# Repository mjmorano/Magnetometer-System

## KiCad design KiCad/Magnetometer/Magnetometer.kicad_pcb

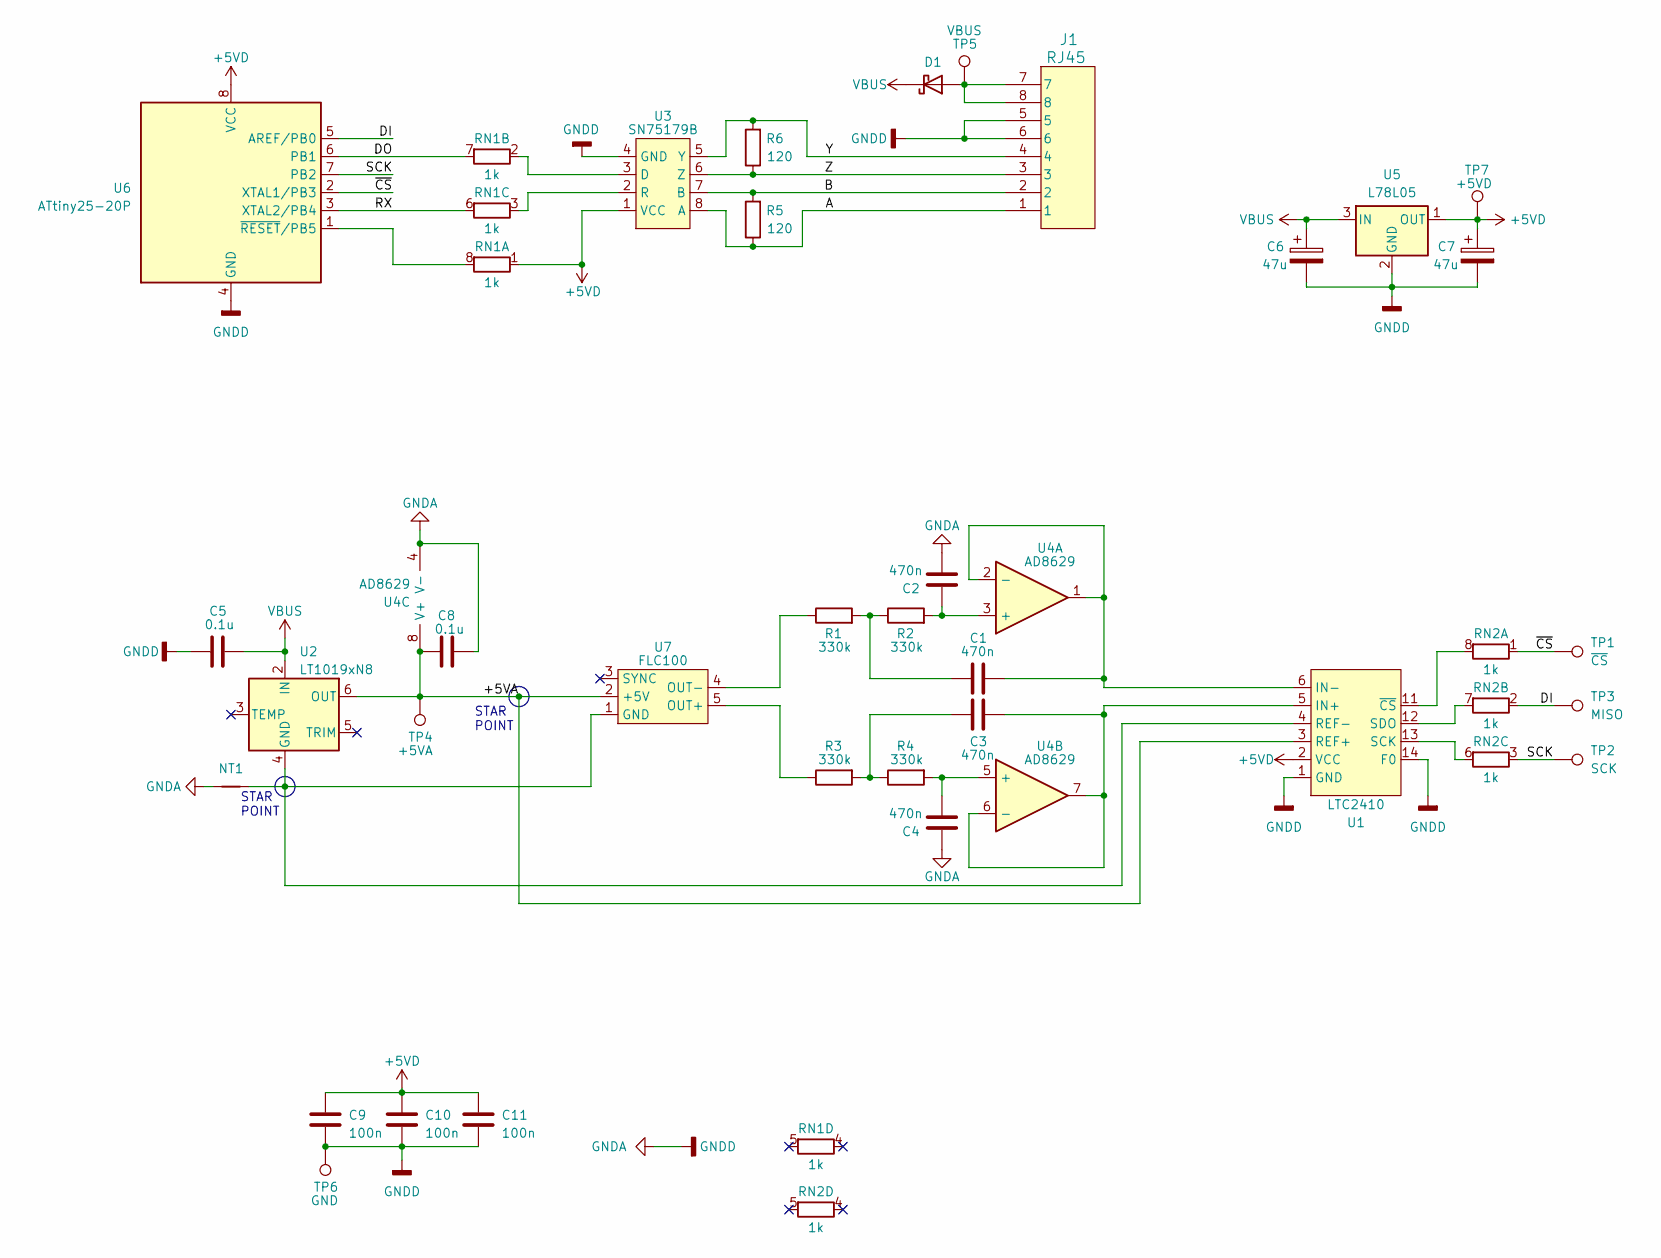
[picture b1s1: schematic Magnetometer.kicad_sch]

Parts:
C1, C2, C3, C4: 470n; C_1206_3216Metric
C5, C8: 0.1u; C_0603_1608Metric
C6, C7: 47u; CP_EIA-6032-28_Kemet-C
C9, C10, C11: 100n; C_0603_1608Metric
D1: D_Schottky; D_SOD-123F
J1: RJ45; rj45
NT1: NetTie-2_SMD_Pad0.5mm
R1, R2, R3, R4: 330k; R_0603_1608Metric
R5, R6: 120; R_0603_1608Metric
RN1, RN2: 1k; R_Array_Convex_4x0603
TP1: ~{CS}; TestPoint_Pad_D1.0mm
TP2: SCK; TestPoint_Pad_D1.0mm
TP3: MISO; TestPoint_Pad_D1.0mm
TP4: +5VA; TestPoint_Pad_D1.0mm
TP5: VBUS; TestPoint_Pad_D1.0mm
TP6: GND; TestPoint_Pad_D1.0mm
TP7: +5VD; TestPoint_Pad_D1.0mm
U1: LTC2410; SSOP-16_3.9x4.9mm_P0.635mm
U2: LT1019xN8; SOIC-8_3.9x4.9mm_P1.27mm
U3: SN75179B; SOIC-8_3.9x4.9mm_P1.27mm
U4: AD8629; SOIC-8_3.9x4.9mm_P1.27mm
U5: L78L05; SOT-89-3
U6: ATtiny25-20P; DIP-8_W7.62mm
U7: FLC100

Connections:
+5VD: C7.1, C9.1, C10.1, C11.1, RN1.1 (R1.1), TP7.1, U1.2 (VCC), U3.1 (VCC), U5.1 (OUT), U6.8 (VCC)
/+5VA: C8.1, TP4.1, U1.3 (REF+), U2.6 (OUT), U4.8 (V+), U7.2 (+5V)
/A: J1.1, R5.1, U3.8 (A)
/B: J1.2, R5.2, U3.7 (B)
/DI: RN2.2 (R2.1), TP3.1, U6.5 (AREF/PB0)
/DO: RN1.7 (R2.2), U6.6 (PB1)
/RX: RN1.6 (R3.2), U6.3 (XTAL2/PB4)
/SCK: RN2.3 (R3.1), TP2.1, U6.7 (PB2)
/Y: J1.4, R6.2, U3.5 (Y)
/Z: J1.3, R6.1, U3.6 (Z)
/~CS: RN2.1 (R1.1), TP1.1, U6.2 (XTAL1/PB3)
GNDA: C2.2, C4.1, C5.2, C6.2, C7.2, C8.2, C9.2, C10.2, C11.2, J1.5, J1.6, NT1.2, TP6.1, U1.1 (GND), U1.7 (GND), U1.8 (GND), U1.9 (GND), U1.10 (GND), U1.14 (F0), U1.15 (GND), U1.16 (GND), U3.4 (GND), U4.4 (V-), U5.2 (GND), U6.4 (GND)
unnamed: C1.2, R1.2, R2.1
unnamed: C3.2, R3.2, R4.1
unnamed: D1.2 (A), J1.7, J1.8, TP5.1
unnamed: RN1.8 (R1.2), U6.1 (~RESET/PB5)
unnamed: RN1.2 (R2.1), U3.3 (D)
unnamed: RN1.3 (R3.1), U3.2 (R)
unnamed: RN2.8 (R1.2), U1.11 (~CS)
unnamed: RN2.7 (R2.2), U1.12 (SDO)
unnamed: RN2.6 (R3.2), U1.13 (SCK)
unnamed: C3.1, U1.5 (IN+), U4.6 (-), U4.7
unnamed: C1.1, U1.6 (IN-), U4.1, U4.2 (-)
unnamed: NT1.1, U1.4 (REF-), U2.4 (GND), U7.1 (GND)
unnamed: C2.1, R2.2, U4.3 (+)
unnamed: C4.2, R4.2, U4.5 (+)
unnamed: R3.1, U7.5 (OUT+)
unnamed: R1.1, U7.4 (OUT-)
VBUS: C5.1, C6.1, D1.1 (K), U2.2 (IN), U5.3 (IN)

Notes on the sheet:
STAR POINT

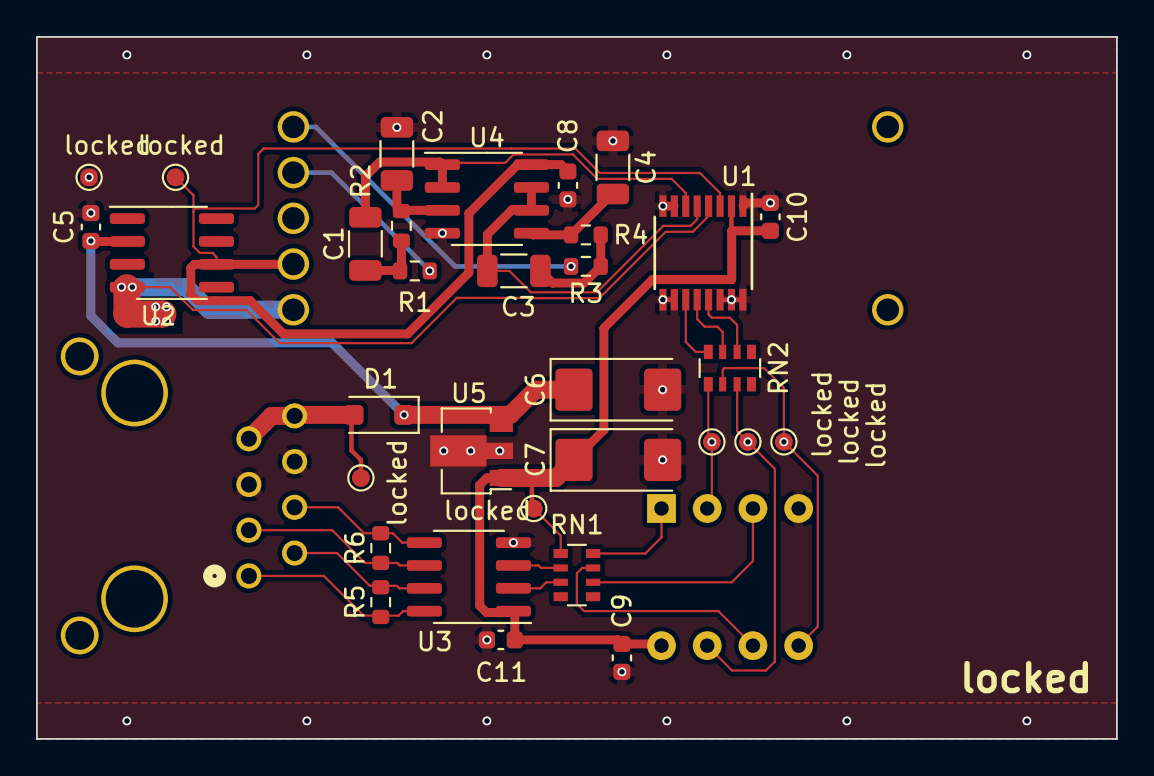
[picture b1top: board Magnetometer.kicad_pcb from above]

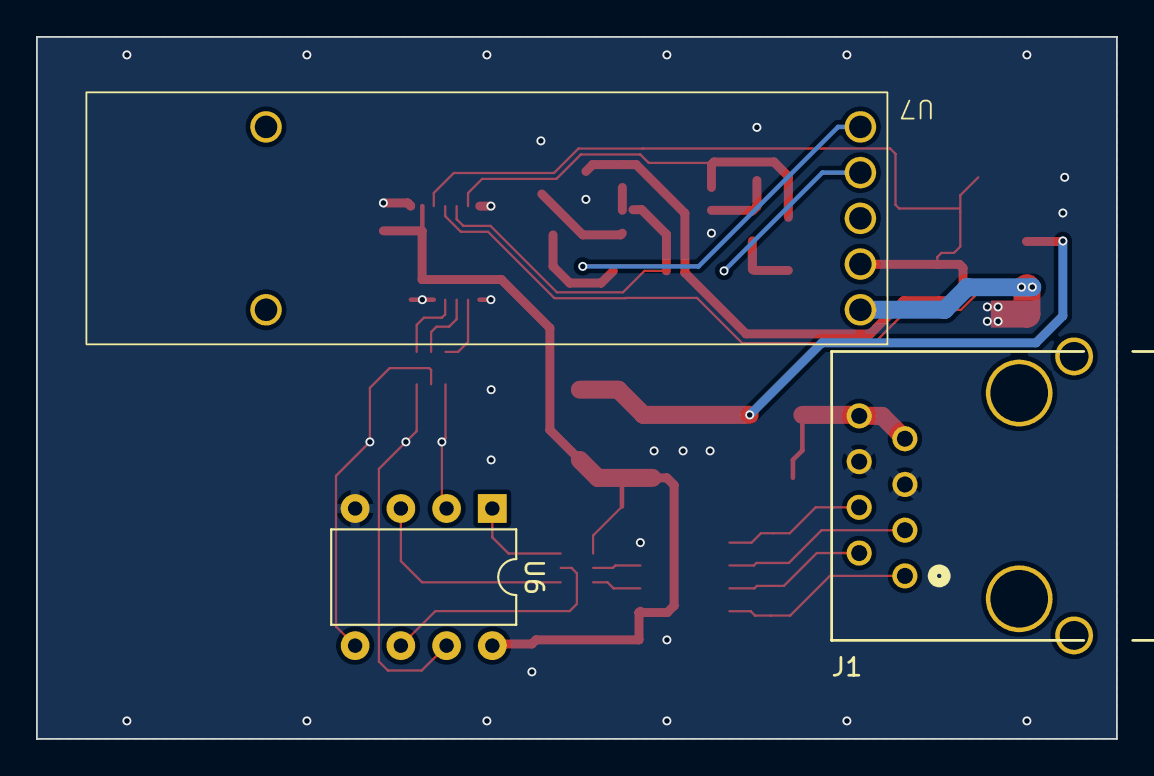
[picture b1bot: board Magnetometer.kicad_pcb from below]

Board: 2 copper layers, 60.0 x 39.0 mm, 36 parts (3 on the bottom side), 29 nets.

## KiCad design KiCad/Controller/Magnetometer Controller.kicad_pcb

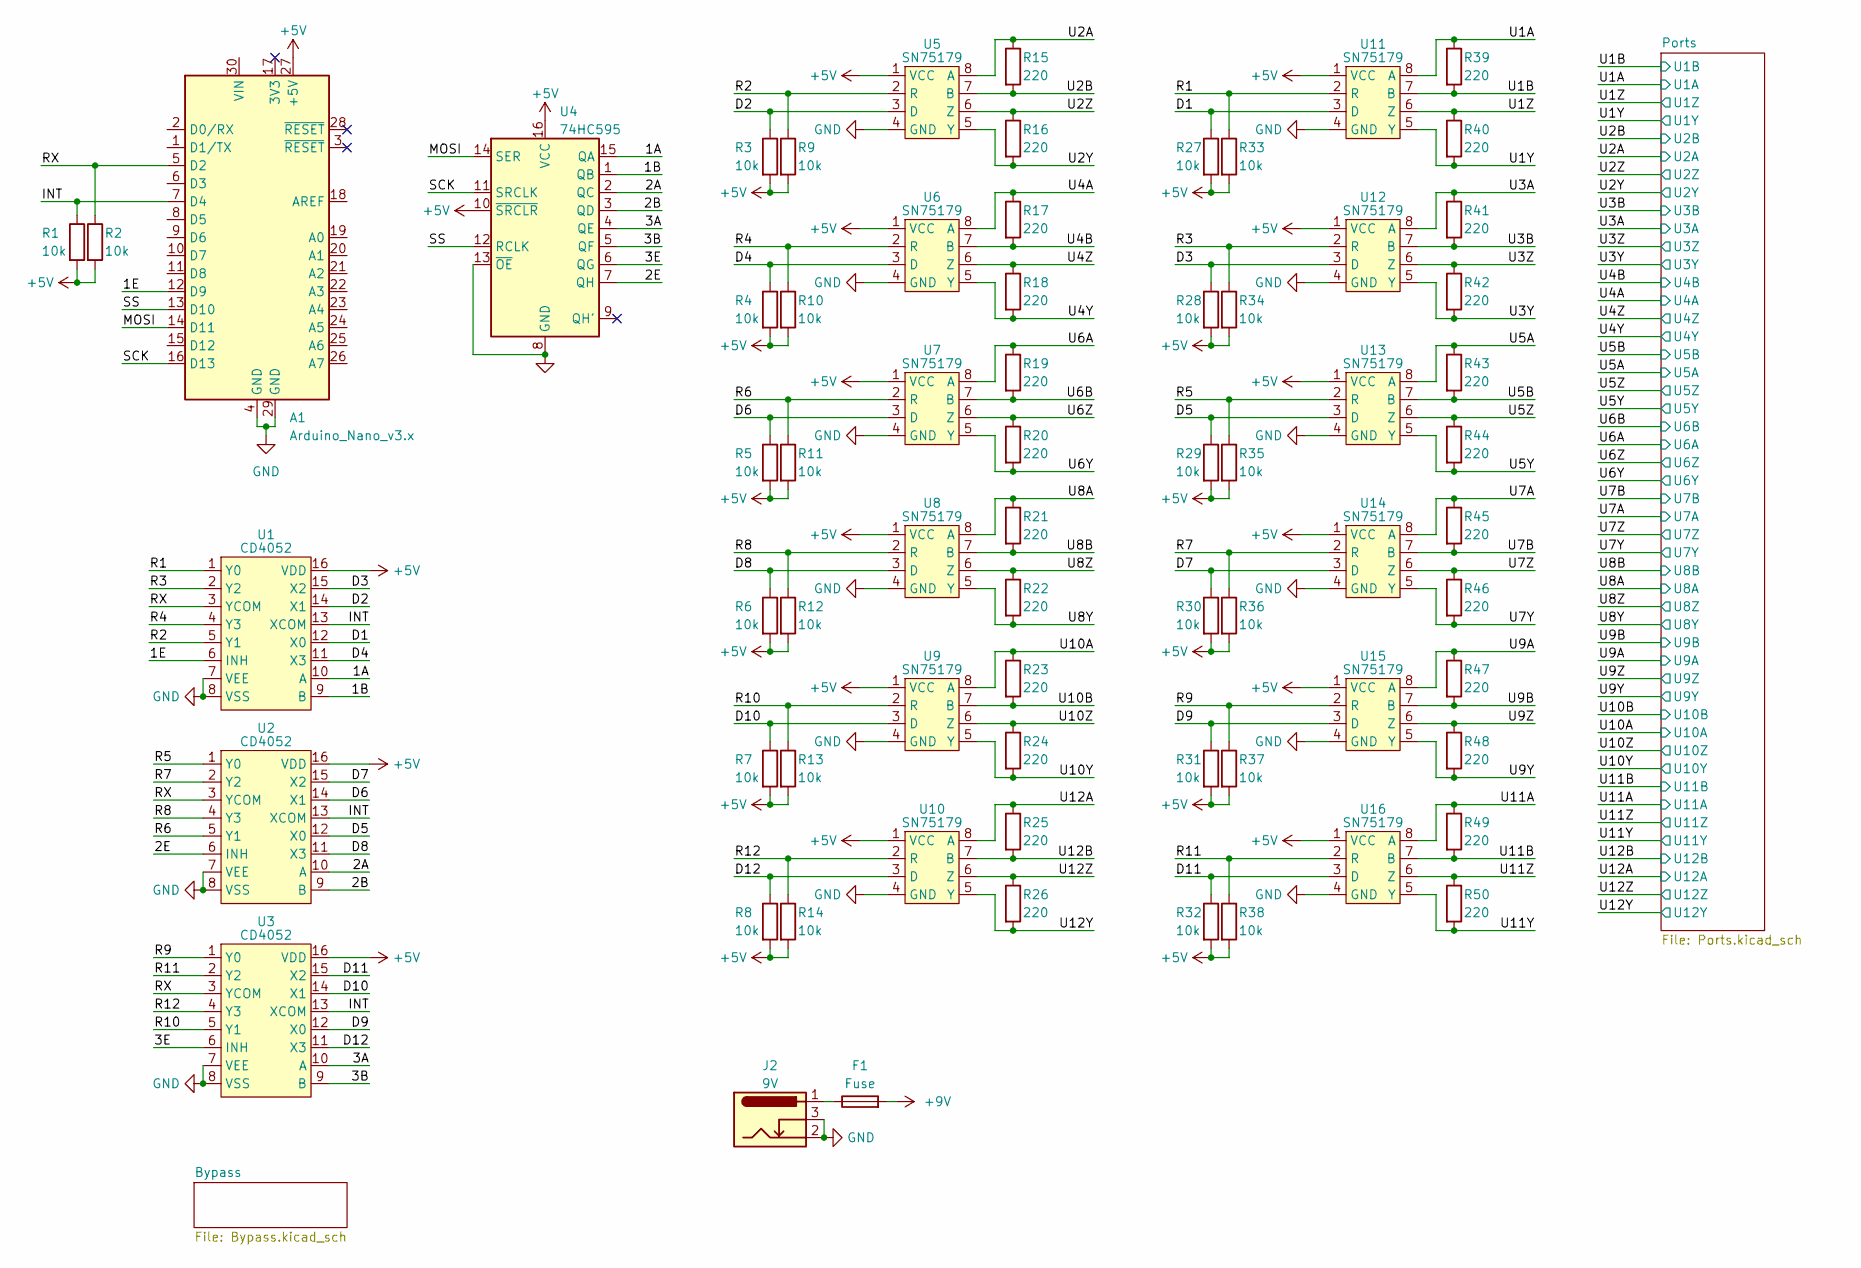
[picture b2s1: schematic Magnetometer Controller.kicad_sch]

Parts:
A1: Arduino_Nano_v3.x; Arduino_Nano
F1: Fuse; 0031.7701.22
J2: 9V; CUI_PJ-002BH
R1, R2, R3, R4, R5, R6, R7, R8, R9, R10, R11, R12, R13, R14, R27, R28, R29, R30, R31, R32, R33, R34, R35, R36, R37, R38: 10k; R_0603_1608Metric
R15, R16, R17, R18, R19, R20, R21, R22, R23, R24, R25, R26, R39, R40, R41, R42, R43, R44, R45, R46, R47, R48, R49, R50: 220; R_0603_1608Metric
U1, U2, U3: CD4052; SOIC-16_3.9x9.9mm_P1.27mm
U4: 74HC595; SOIC-16_3.9x9.9mm_P1.27mm
U5, U6, U7, U8, U9, U10, U11, U12, U13, U14, U15, U16: SN75179; SOIC-8_3.9x4.9mm_P1.27mm

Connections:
+5V: A1.27 (+5V), R1.2, R2.2, R3.2, R4.2, R5.2, R6.2, R7.2, R8.2, R9.2, R10.2, R11.2, R12.2, R13.2, R14.2, R27.2, R28.2, R29.2, R30.2, R31.2, R32.2, R33.2, R34.2, R35.2, R36.2, R37.2, R38.2, U1.16 (VDD), U2.16 (VDD), U3.16 (VDD), U4.10 (~SRCLR), U4.16 (VCC), U5.1 (VCC), U6.1 (VCC), U7.1 (VCC), U8.1 (VCC), U9.1 (VCC), U10.1 (VCC), U11.1 (VCC), U12.1 (VCC), U13.1 (VCC), U14.1 (VCC), U15.1 (VCC), U16.1 (VCC); also elsewhere on the board
+9V: F1.2; also elsewhere on the board
/1A: U1.10 (A), U4.15 (QA)
/1B: U1.9 (B), U4.1 (QB)
/1E: A1.12 (D9), U1.6 (INH)
/2A: U2.10 (A), U4.2 (QC)
/2B: U2.9 (B), U4.3 (QD)
/2E: U2.6 (INH), U4.7 (QH)
/3A: U3.10 (A), U4.4 (QE)
/3B: U3.9 (B), U4.5 (QF)
/3E: U3.6 (INH), U4.6 (QG)
/D1: R27.1, U1.12 (X0), U11.3 (D)
/D2: R3.1, U1.14 (X1), U5.3 (D)
/D3: R28.1, U1.15 (X2), U12.3 (D)
/D4: R4.1, U1.11 (X3), U6.3 (D)
/D5: R29.1, U2.12 (X0), U13.3 (D)
/D6: R5.1, U2.14 (X1), U7.3 (D)
/D7: R30.1, U2.15 (X2), U14.3 (D)
/D8: R6.1, U2.11 (X3), U8.3 (D)
/D9: R31.1, U3.12 (X0), U15.3 (D)
/D10: R7.1, U3.14 (X1), U9.3 (D)
/D11: R32.1, U3.15 (X2), U16.3 (D)
/D12: R8.1, U3.11 (X3), U10.3 (D)
/INT: A1.7 (D4), R1.1, U1.13 (XCOM), U2.13 (XCOM), U3.13 (XCOM)
/MOSI: A1.14 (D11), U4.14 (SER)
/R1: R33.1, U1.1 (Y0), U11.2 (R)
/R2: R9.1, U1.5 (Y1), U5.2 (R)
/R3: R34.1, U1.2 (Y2), U12.2 (R)
/R4: R10.1, U1.4 (Y3), U6.2 (R)
/R5: R35.1, U2.1 (Y0), U13.2 (R)
/R6: R11.1, U2.5 (Y1), U7.2 (R)
/R7: R36.1, U2.2 (Y2), U14.2 (R)
/R8: R12.1, U2.4 (Y3), U8.2 (R)
/R9: R37.1, U3.1 (Y0), U15.2 (R)
/R10: R13.1, U3.5 (Y1), U9.2 (R)
/R11: R38.1, U3.2 (Y2), U16.2 (R)
/R12: R14.1, U3.4 (Y3), U10.2 (R)
/RX: A1.5 (D2), R2.1, U1.3 (YCOM), U2.3 (YCOM), U3.3 (YCOM)
/SCK: A1.16 (D13), U4.11 (SRCLK)
/SS: A1.13 (D10), U4.12 (RCLK)
/U1A: R39.1, U11.8 (A); also elsewhere on the board
/U1B: R39.2, U11.7 (B); also elsewhere on the board
/U1Y: R40.2, U11.5 (Y); also elsewhere on the board
/U1Z: R40.1, U11.6 (Z); also elsewhere on the board
/U2A: R15.1, U5.8 (A); also elsewhere on the board
/U2B: R15.2, U5.7 (B); also elsewhere on the board
/U2Y: R16.2, U5.5 (Y); also elsewhere on the board
/U2Z: R16.1, U5.6 (Z); also elsewhere on the board
/U3A: R41.1, U12.8 (A); also elsewhere on the board
/U3B: R41.2, U12.7 (B); also elsewhere on the board
/U3Y: R42.2, U12.5 (Y); also elsewhere on the board
/U3Z: R42.1, U12.6 (Z); also elsewhere on the board
/U4A: R17.1, U6.8 (A); also elsewhere on the board
/U4B: R17.2, U6.7 (B); also elsewhere on the board
/U4Y: R18.2, U6.5 (Y); also elsewhere on the board
/U4Z: R18.1, U6.6 (Z); also elsewhere on the board
/U5A: R43.1, U13.8 (A); also elsewhere on the board
/U5B: R43.2, U13.7 (B); also elsewhere on the board
/U5Y: R44.2, U13.5 (Y); also elsewhere on the board
/U5Z: R44.1, U13.6 (Z); also elsewhere on the board
/U6A: R19.1, U7.8 (A); also elsewhere on the board
/U6B: R19.2, U7.7 (B); also elsewhere on the board
/U6Y: R20.2, U7.5 (Y); also elsewhere on the board
/U6Z: R20.1, U7.6 (Z); also elsewhere on the board
/U7A: R45.1, U14.8 (A); also elsewhere on the board
/U7B: R45.2, U14.7 (B); also elsewhere on the board
/U7Y: R46.2, U14.5 (Y); also elsewhere on the board
/U7Z: R46.1, U14.6 (Z); also elsewhere on the board
/U8A: R21.1, U8.8 (A); also elsewhere on the board
/U8B: R21.2, U8.7 (B); also elsewhere on the board
/U8Y: R22.2, U8.5 (Y); also elsewhere on the board
/U8Z: R22.1, U8.6 (Z); also elsewhere on the board
/U9A: R47.1, U15.8 (A); also elsewhere on the board
/U9B: R47.2, U15.7 (B); also elsewhere on the board
/U9Y: R48.2, U15.5 (Y); also elsewhere on the board
/U9Z: R48.1, U15.6 (Z); also elsewhere on the board
/U10A: R23.1, U9.8 (A); also elsewhere on the board
/U10B: R23.2, U9.7 (B); also elsewhere on the board
/U10Y: R24.2, U9.5 (Y); also elsewhere on the board
/U10Z: R24.1, U9.6 (Z); also elsewhere on the board
/U11A: R49.1, U16.8 (A); also elsewhere on the board
/U11B: R49.2, U16.7 (B); also elsewhere on the board
/U11Y: R50.2, U16.5 (Y); also elsewhere on the board
/U11Z: R50.1, U16.6 (Z); also elsewhere on the board
/U12A: R25.1, U10.8 (A); also elsewhere on the board
/U12B: R25.2, U10.7 (B); also elsewhere on the board
/U12Y: R26.2, U10.5 (Y); also elsewhere on the board
/U12Z: R26.1, U10.6 (Z); also elsewhere on the board
GND: A1.4 (GND), A1.29 (GND), J2.2, J2.3, U1.7 (VEE), U1.8 (VSS), U2.7 (VEE), U2.8 (VSS), U3.7 (VEE), U3.8 (VSS), U4.8 (GND), U4.13 (~OE), U5.4 (GND), U6.4 (GND), U7.4 (GND), U8.4 (GND), U9.4 (GND), U10.4 (GND), U11.4 (GND), U12.4 (GND), U13.4 (GND), U14.4 (GND), U15.4 (GND), U16.4 (GND); also elsewhere on the board
unnamed: F1.1, J2.1

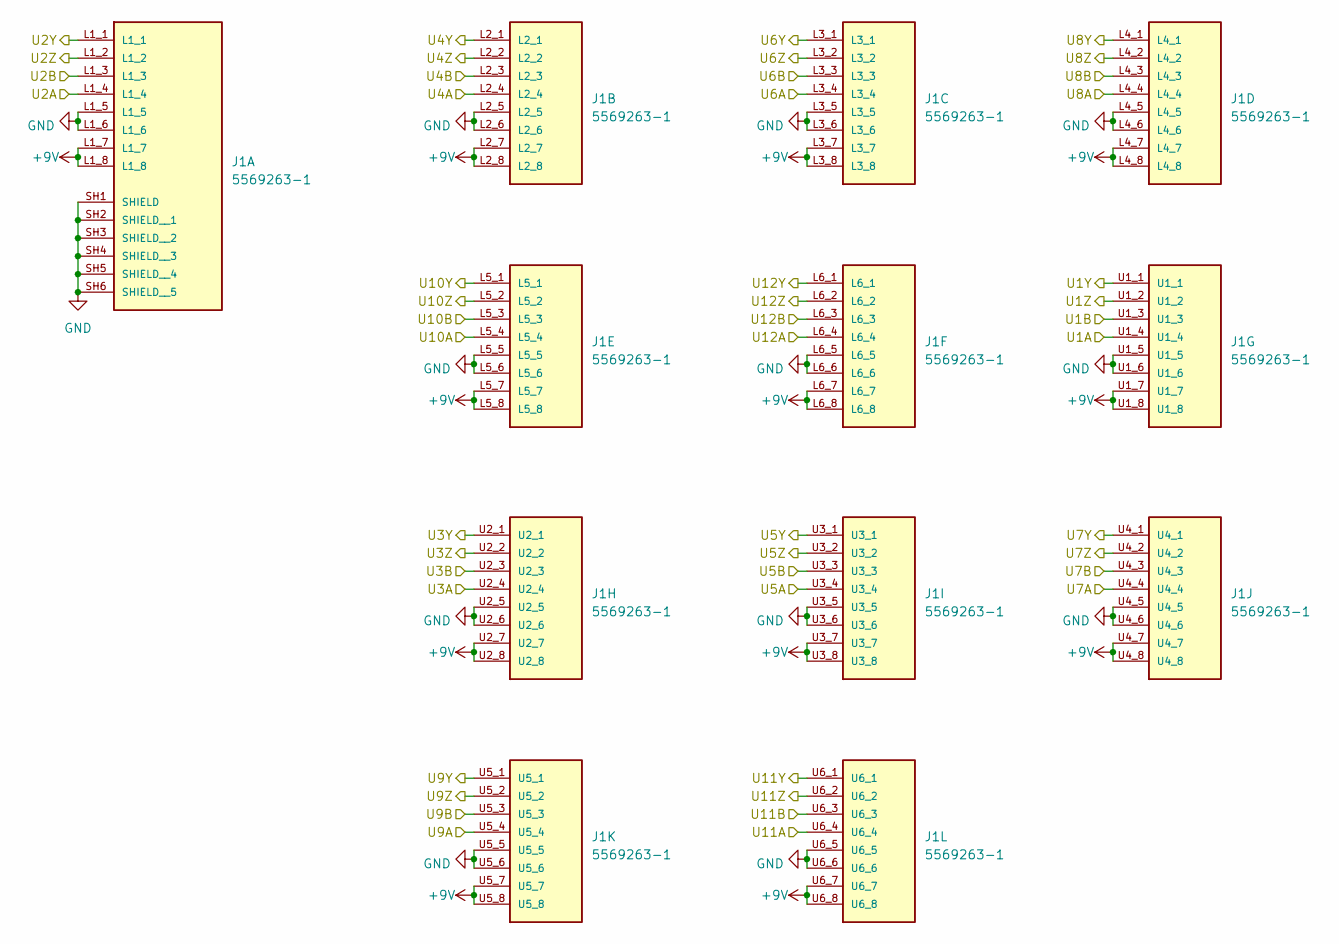
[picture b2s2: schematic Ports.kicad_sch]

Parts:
J1: 5569263-1; TE_5569263-1; PARTREV B3

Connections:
+9V: J1.L1_7, J1.L1_8, J1.L2_7, J1.L2_8, J1.L3_7, J1.L3_8, J1.L4_7, J1.L4_8, J1.L5_7, J1.L5_8, J1.L6_7, J1.L6_8, J1.U1_7, J1.U1_8, J1.U2_7, J1.U2_8, J1.U3_7, J1.U3_8, J1.U4_7, J1.U4_8, J1.U5_7, J1.U5_8, J1.U6_7, J1.U6_8; also elsewhere on the board
/U1A: J1.U1_4; also elsewhere on the board
/U1B: J1.U1_3; also elsewhere on the board
/U1Y: J1.U1_1; also elsewhere on the board
/U1Z: J1.U1_2; also elsewhere on the board
/U2A: J1.L1_4; also elsewhere on the board
/U2B: J1.L1_3; also elsewhere on the board
/U2Y: J1.L1_1; also elsewhere on the board
/U2Z: J1.L1_2; also elsewhere on the board
/U3A: J1.U2_4; also elsewhere on the board
/U3B: J1.U2_3; also elsewhere on the board
/U3Y: J1.U2_1; also elsewhere on the board
/U3Z: J1.U2_2; also elsewhere on the board
/U4A: J1.L2_4; also elsewhere on the board
/U4B: J1.L2_3; also elsewhere on the board
/U4Y: J1.L2_1; also elsewhere on the board
/U4Z: J1.L2_2; also elsewhere on the board
/U5A: J1.U3_4; also elsewhere on the board
/U5B: J1.U3_3; also elsewhere on the board
/U5Y: J1.U3_1; also elsewhere on the board
/U5Z: J1.U3_2; also elsewhere on the board
/U6A: J1.L3_4; also elsewhere on the board
/U6B: J1.L3_3; also elsewhere on the board
/U6Y: J1.L3_1; also elsewhere on the board
/U6Z: J1.L3_2; also elsewhere on the board
/U7A: J1.U4_4; also elsewhere on the board
/U7B: J1.U4_3; also elsewhere on the board
/U7Y: J1.U4_1; also elsewhere on the board
/U7Z: J1.U4_2; also elsewhere on the board
/U8A: J1.L4_4; also elsewhere on the board
/U8B: J1.L4_3; also elsewhere on the board
/U8Y: J1.L4_1; also elsewhere on the board
/U8Z: J1.L4_2; also elsewhere on the board
/U9A: J1.U5_4; also elsewhere on the board
/U9B: J1.U5_3; also elsewhere on the board
/U9Y: J1.U5_1; also elsewhere on the board
/U9Z: J1.U5_2; also elsewhere on the board
/U10A: J1.L5_4; also elsewhere on the board
/U10B: J1.L5_3; also elsewhere on the board
/U10Y: J1.L5_1; also elsewhere on the board
/U10Z: J1.L5_2; also elsewhere on the board
/U11A: J1.U6_4; also elsewhere on the board
/U11B: J1.U6_3; also elsewhere on the board
/U11Y: J1.U6_1; also elsewhere on the board
/U11Z: J1.U6_2; also elsewhere on the board
/U12A: J1.L6_4; also elsewhere on the board
/U12B: J1.L6_3; also elsewhere on the board
/U12Y: J1.L6_1; also elsewhere on the board
/U12Z: J1.L6_2; also elsewhere on the board
GND: J1.L1_5, J1.L1_6, J1.L2_5, J1.L2_6, J1.L3_5, J1.L3_6, J1.L4_5, J1.L4_6, J1.L5_5, J1.L5_6, J1.L6_5, J1.L6_6, J1.SH1 (SHIELD), J1.SH2 (SHIELD__1), J1.SH3 (SHIELD__2), J1.SH4 (SHIELD__3), J1.SH5 (SHIELD__4), J1.SH6 (SHIELD__5), J1.U1_5, J1.U1_6, J1.U2_5, J1.U2_6, J1.U3_5, J1.U3_6, J1.U4_5, J1.U4_6, J1.U5_5, J1.U5_6, J1.U6_5, J1.U6_6; also elsewhere on the board

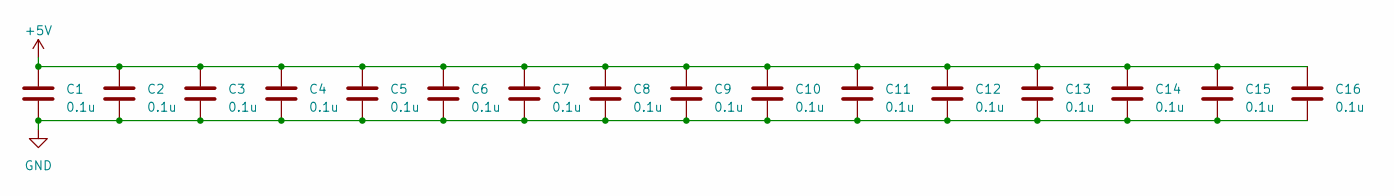
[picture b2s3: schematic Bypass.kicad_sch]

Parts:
C1, C2, C3, C4, C5, C6, C7, C8, C9, C10, C11, C12, C13, C14, C15, C16: 0.1u; C_0603_1608Metric

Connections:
+5V: C1.1, C2.1, C3.1, C4.1, C5.1, C6.1, C7.1, C8.1, C9.1, C10.1, C11.1, C12.1, C13.1, C14.1, C15.1, C16.1; also elsewhere on the board
GND: C1.2, C2.2, C3.2, C4.2, C5.2, C6.2, C7.2, C8.2, C9.2, C10.2, C11.2, C12.2, C13.2, C14.2, C15.2, C16.2; also elsewhere on the board

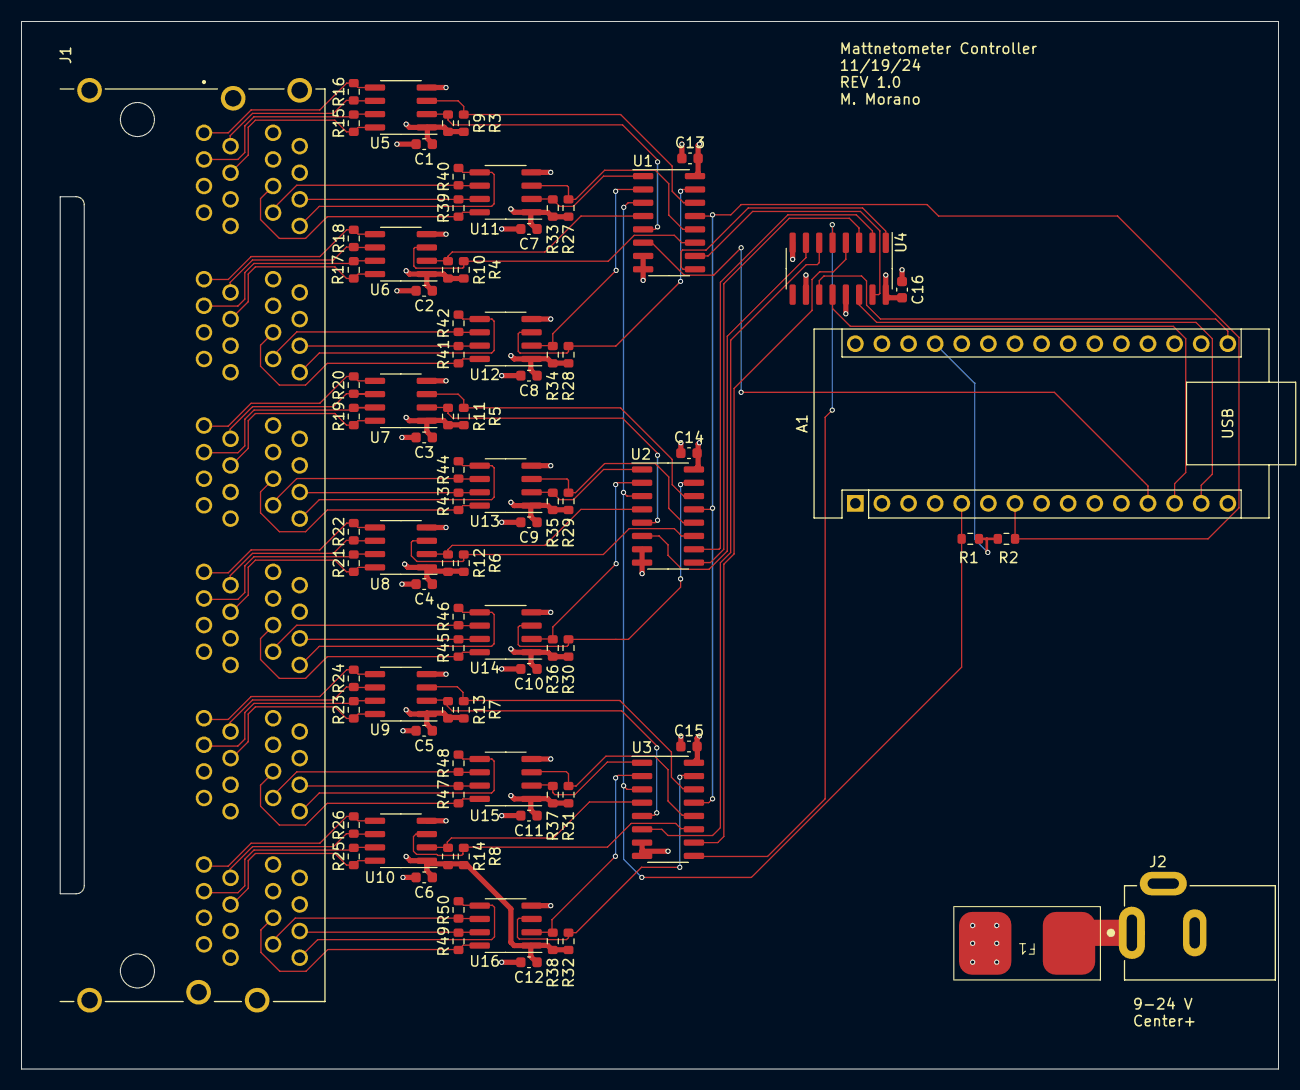
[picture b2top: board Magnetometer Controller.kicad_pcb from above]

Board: 4 copper layers, 120.0 x 100.0 mm, 86 parts (0 on the bottom side), 90 nets.

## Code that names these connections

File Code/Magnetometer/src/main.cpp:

/*
	Author: M Morano
	Date: 1/29/2025

	This is code for the microcontroller that reads the ADC. All it does is read the ADC every 250 ms, and
	transmits it to the controller when asked to. Most of it is pretty self explanatory because the SPI and
	UART interfaces are bit-banged. 
*/

#include <avr/io.h>
#include <util/delay.h>
#include <avr/interrupt.h>

#define USCK PB2
#define DO PB1
#define DI PB0
#define SS PB3
#define TRIG PB4
#define bitTime 100                 // used for timing the Serial output

volatile uint16_t timerCount = 0;	// used for setting the ADC sample rate
volatile uint8_t adcCode[4];		// 4 bytes to store the ADC value
volatile bool flag = false;        	// flag for a transmit request

ISR(PCINT0_vect) {

	// Check for falling edge
	if( ~PINB & (1 << TRIG) )
		flag = true; // set transmit flag	
}

ISR(TIMER0_COMPA_vect) {
	
    timerCount++; // increment timer every 100 us
	
}

void transmit(uint8_t outByte) {

	// send start bit
	PORTB |= (1 << DO);  
	_delay_us(bitTime); 
	PORTB &= ~(1 << DO);
	_delay_us(bitTime);

	// bit bang data
	for(uint8_t i = 0; i < 8 ; i++) {
		outByte & (1 << i) ? PORTB |= (1 << DO) : PORTB &= ~(1 << DO);
		_delay_us(bitTime);
	}

	// send stop bit and add short delay before sending next byte
	PORTB |= (1 << DO);
	_delay_us(bitTime);
	
}

// 
void readAdc() {
	
	PORTB &= ~(1 << SS); // pull SS low
	
    // loop four times to get 32 data bits from ADC
	for(uint8_t i = 0; i < 4; i++) {
		
		for(uint8_t j = 0; j < 8; j++) {
			
			(PINB & (1 << DI)) ? adcCode[i] |= (1 << (7-j)) : adcCode[i] &= ~(1 << (7-j)); // read bit from ADC
			PORTB |= (1 << USCK);   // toggle USCK to shift out next bit
			PORTB &= ~(1 << USCK);
			
		}
		
	}
	
	PORTB |= (1 << SS); // put SS high
	
}

int main(void) {

    MCUCR |= (1 << ISC01);                              // falling edge interrupt
    GIMSK |= (1 << PCIE);                               // enable pin change interrupt
    PCMSK |= (1 << TRIG);                               // enable interrupts on TRIG pin
    DDRB |= (1 << DO) | (1 << USCK) | (1 << SS);        // configure pins for output
    DDRB &= ~(1 << TRIG) | ~(1 << DI);                  // configure pins for input
    PORTB |= (1 << TRIG) | (1 << DI);                   // enable pullup resistors
	PORTB |= (1 << SS) | (1 << DO);						// idle output pins high
	PORTB &= ~(1 << USCK);								// idle USCK LOW
    TCCR0A |= (1 << WGM01);                             // configure timer0 for CTC mode
    TCCR0B |= (1 << CS01);                              // configure prescaler for div/8 = 1 MHz
    OCR0A = 99;                                         // configure for further div/100 = 10 KHz
    TIMSK |= (1 << OCIE0A);                             // enable timer0 interrupts
	sei();												// enable interrupts

    while(1) {
		
		// read adc at 4 Hz
    	if (timerCount >= 2499){

			readAdc();
			timerCount = 0; // reset timer

      	}
		
		// wait for the transmit flag to be set
		if (flag){

			// send four bytes from ADC
			for (uint8_t i = 0; i < 4; i++)
				transmit(adcCode[i]);
		
			flag = false; // clear transmit flag
			
		}
			
	}
	
}

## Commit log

2025-01-29 Added KiCad backups to gitignore
2025-01-29 Removed KiCad backups
2025-01-29 Added datasheets
2025-02-03 Started adding finishing touches
2025-02-03 Fixed some small style problems
2025-02-03 Cleaned up unused stuff
2025-02-03 Added .step models for everything
2025-02-11 Fixed some problems with the log file
2025-02-11 Edited some comments
2025-02-11 Changed the slider lower limits
2025-04-28 Added ArduinoISP configuration
2025-04-28 Updated for new dash version
2025-04-28 Added more comments
2025-04-28 Fixed the upload not setting the fuses correctly
2025-04-28 Fixed an alignment problem with the graphs
2025-04-28 Reduced the grid gap a little bit
2025-04-28 Fixed alignment in both plot size modes
2025-05-21 Fixed dash version being wrong
2025-05-21 Fixed yaxis title not changing color in dark mode
